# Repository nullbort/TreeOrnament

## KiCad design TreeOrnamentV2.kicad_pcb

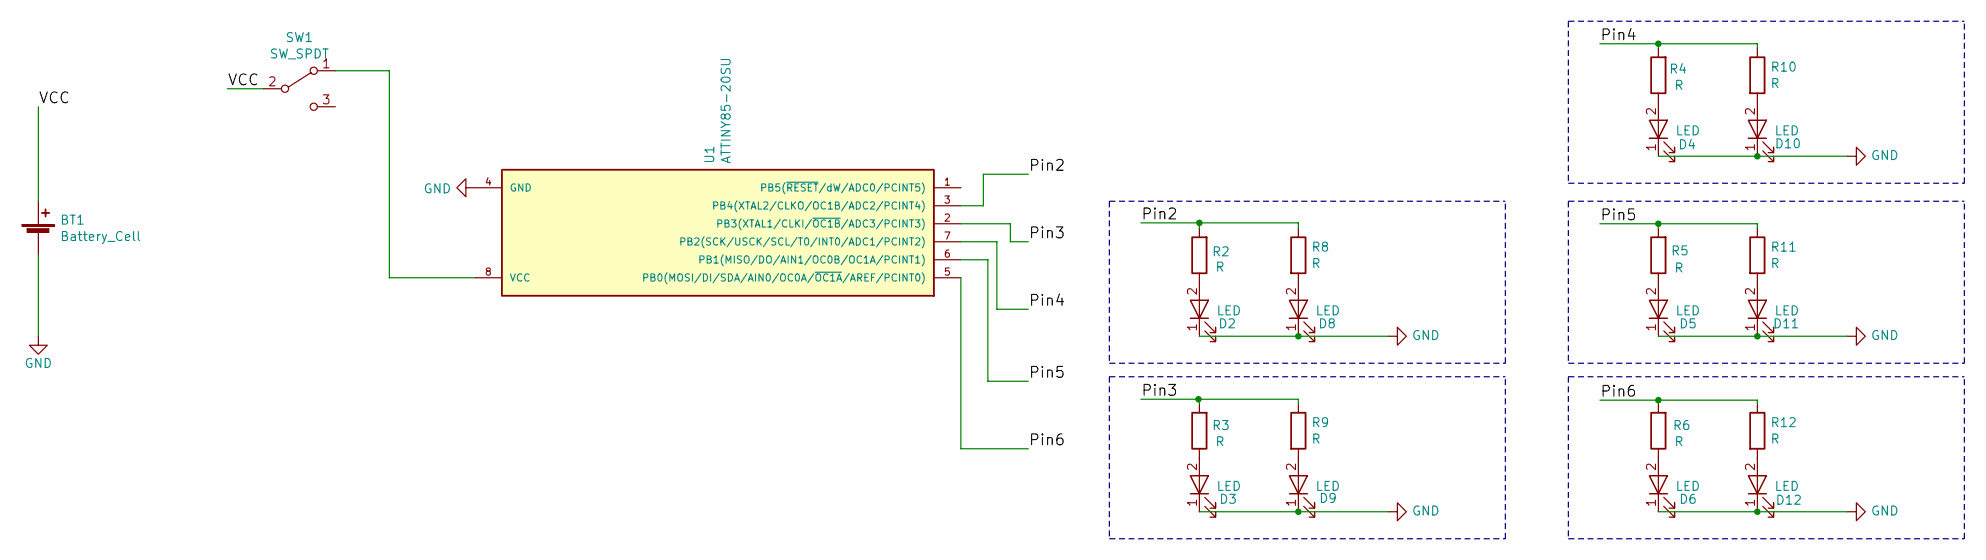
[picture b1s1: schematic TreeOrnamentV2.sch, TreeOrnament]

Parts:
BT1: Battery_Cell
D2, D3, D4, D5, D6, D8, D9, D10, D11, D12: LED; LED_0805
R2, R3, R4, R5, R6, R8, R9, R10, R11, R12: R; R_0603_HandSoldering
SW1: SW_SPDT; CL-SB-12B-01T
U1: ATTINY85-20SU; SOIC-8_3.9x4.9mm_Pitch1.27mm

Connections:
/Pin2: R2.2, R8.1, U1.3 (PB4(XTAL2/CLKO/OC1B/ADC2/PCINT4))
/Pin3: R3.2, R9.1, U1.2 (PB3(XTAL1/CLKI/~OC1B~/ADC3/PCINT3))
/Pin4: R4.2, R10.1, U1.7 (PB2(SCK/USCK/SCL/T0/INT0/ADC1/PCINT2))
/Pin5: R5.2, R11.1, U1.6 (PB1(MISO/DO/AIN1/OC0B/OC1A/PCINT1))
/Pin6: R6.2, R12.1, U1.5 (PB0(MOSI/DI/SDA/AIN0/OC0A/~OC1A~/AREF/P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)
/VCC: BT1.1 (+), SW1.2 (B)
GND: BT1.2 (-), D2.1 (K), D3.1 (K), D4.1 (K), D5.1 (K), D6.1 (K), D8.1 (K), D9.1 (K), D10.1 (K), D11.1 (K), D12.1 (K), U1.4 (GND)
unnamed: D2.2 (A), R2.1
unnamed: D3.2 (A), R3.1
unnamed: D4.2 (A), R4.1
unnamed: D5.2 (A), R5.1
unnamed: D6.2 (A), R6.1
unnamed: D8.2 (A), R8.2
unnamed: D9.2 (A), R9.2
unnamed: D10.2 (A), R10.2
unnamed: D11.2 (A), R11.2
unnamed: D12.2 (A), R12.2
unnamed: SW1.1 (A), U1.8 (VCC)

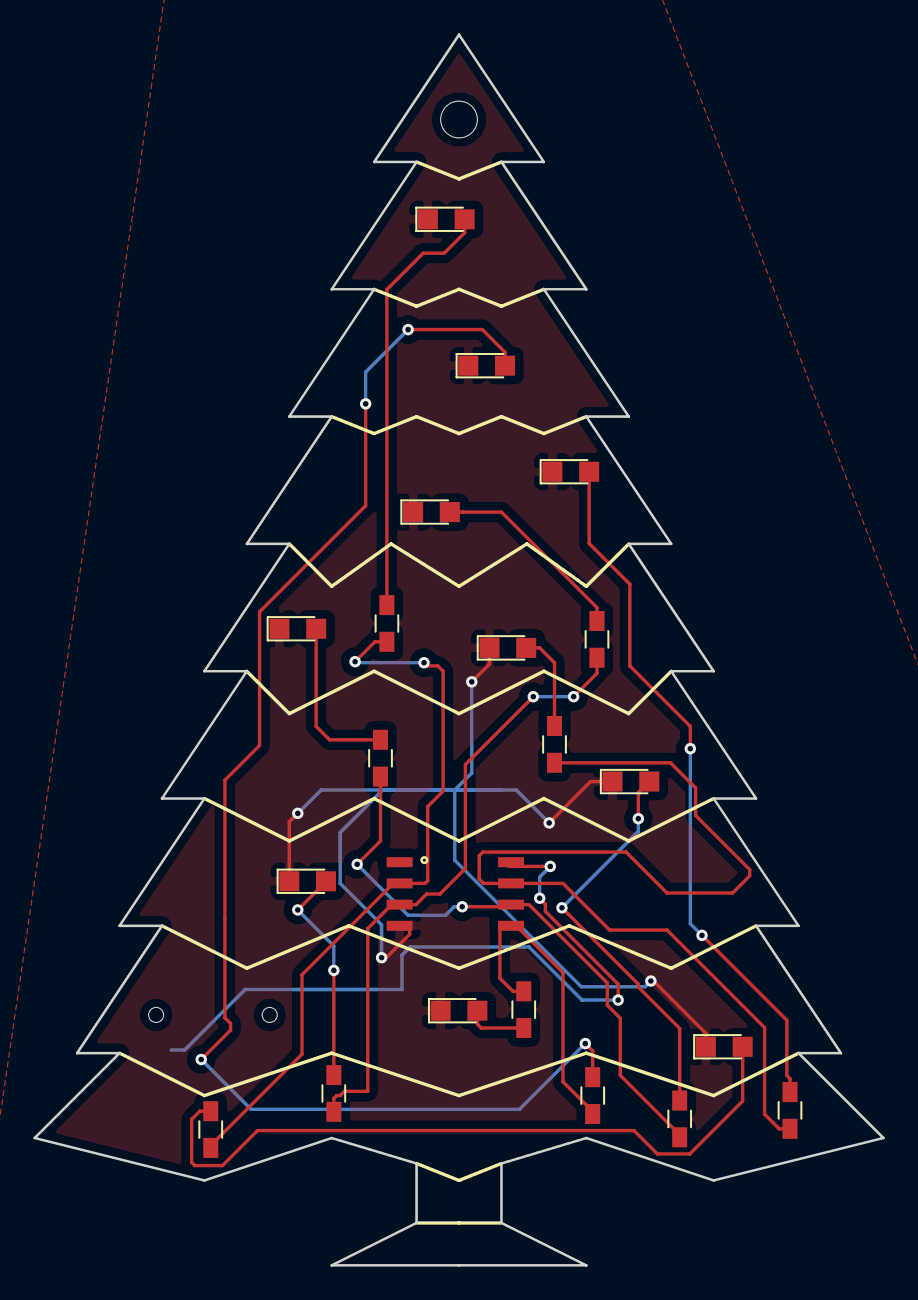
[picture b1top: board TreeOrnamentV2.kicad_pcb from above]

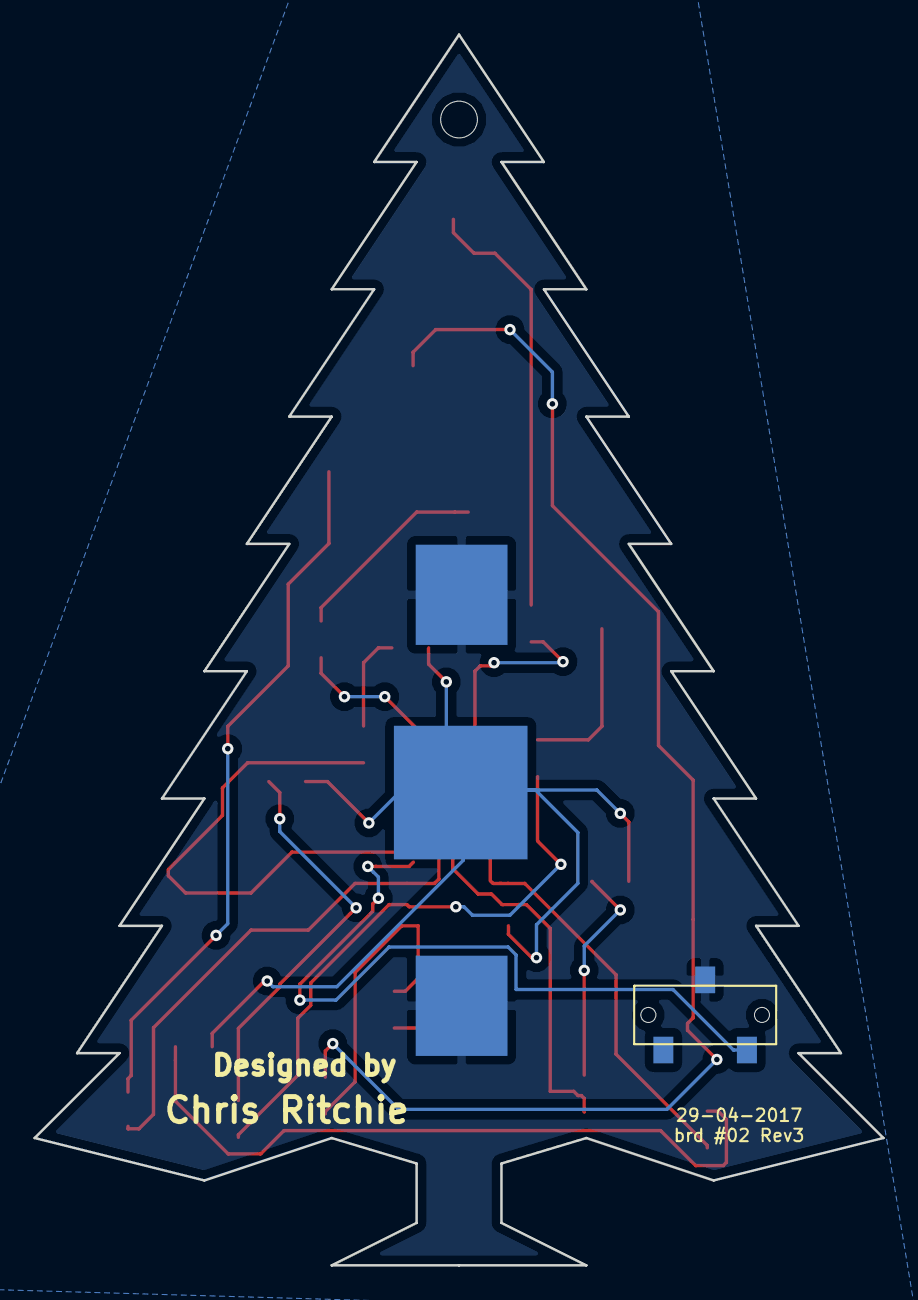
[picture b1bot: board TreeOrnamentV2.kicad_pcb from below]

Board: 2 copper layers, 50.8 x 73.7 mm, 23 parts (2 on the bottom side), 18 nets.

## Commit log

2017-07-08 Add Files
2017-07-08 Saved In New KiCAD Version
2017-07-15 Update ATTiny Footprint
    Update footprint for ATTiny
    Add price spreadsheet
2017-07-29 Fix Switch Track
    Move track from switch to power ATTiny so it doesn't cross VCC pad of battery holder
2017-11-12 KiCad Symbol Update
    Update to how KiCad uses sybols
